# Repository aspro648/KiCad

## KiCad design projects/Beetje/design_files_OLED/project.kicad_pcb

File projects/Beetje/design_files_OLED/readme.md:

Beetje OLED

Project website: https://hackaday.io/project/160638-beetje-bloks

Based on SparkFun's [Micro OLED Breakout](https://www.sparkfun.com/products/13003)

Bill Of Materials
----------------

- 1 ea., Perfect Purple PCB from OSH Park, with not so perfect layout from [design_files](design_files/) folder.
- 1 ea., CrystalFonts display CFAL4864A, https://www.crystalfontz.com/product/cfal6448a066bw-64x48-small-graphic-oled
- 2 ea., R1, R2 RES 4K7 OHM 5% 0805, https://www.digikey.com/short/j2d0wd 
- 4 ea., R3 - R6 RES 10K OHM 5% 0805, 
- 1 ea., C1 CAP 1uF 0805, https://www.digikey.com/short/jwjfn1
- 2 ea., C2, C3 CAP CER 0.1UF 0805
- 1 ea., CONN FPC TOP 12POS 0.50MM R/A, TE 1-1734839-2, https://www.digikey.com/short/pzh9vc

Optional
----------------

- Headers

Revisions
------------------

License
----------------
[Attribution-ShareAlike 3.0 United States (CC BY-SA 3.0 US)](https://creativecommons.org/licenses/by-sa/3.0/us/)

You are free to:

- Share — copy and redistribute the material in any medium or format
- Adapt — remix, transform, and build upon the material

Under the following terms:

- Attribution — You must give appropriate credit, provide a link to the license, and indicate if changes were made. You may do so in any reasonable manner, but not in any way that suggests the licensor endorses you or your use.
- ShareAlike — If you remix, transform, or build upon the material, you must distribute your contributions under the same license as the original.

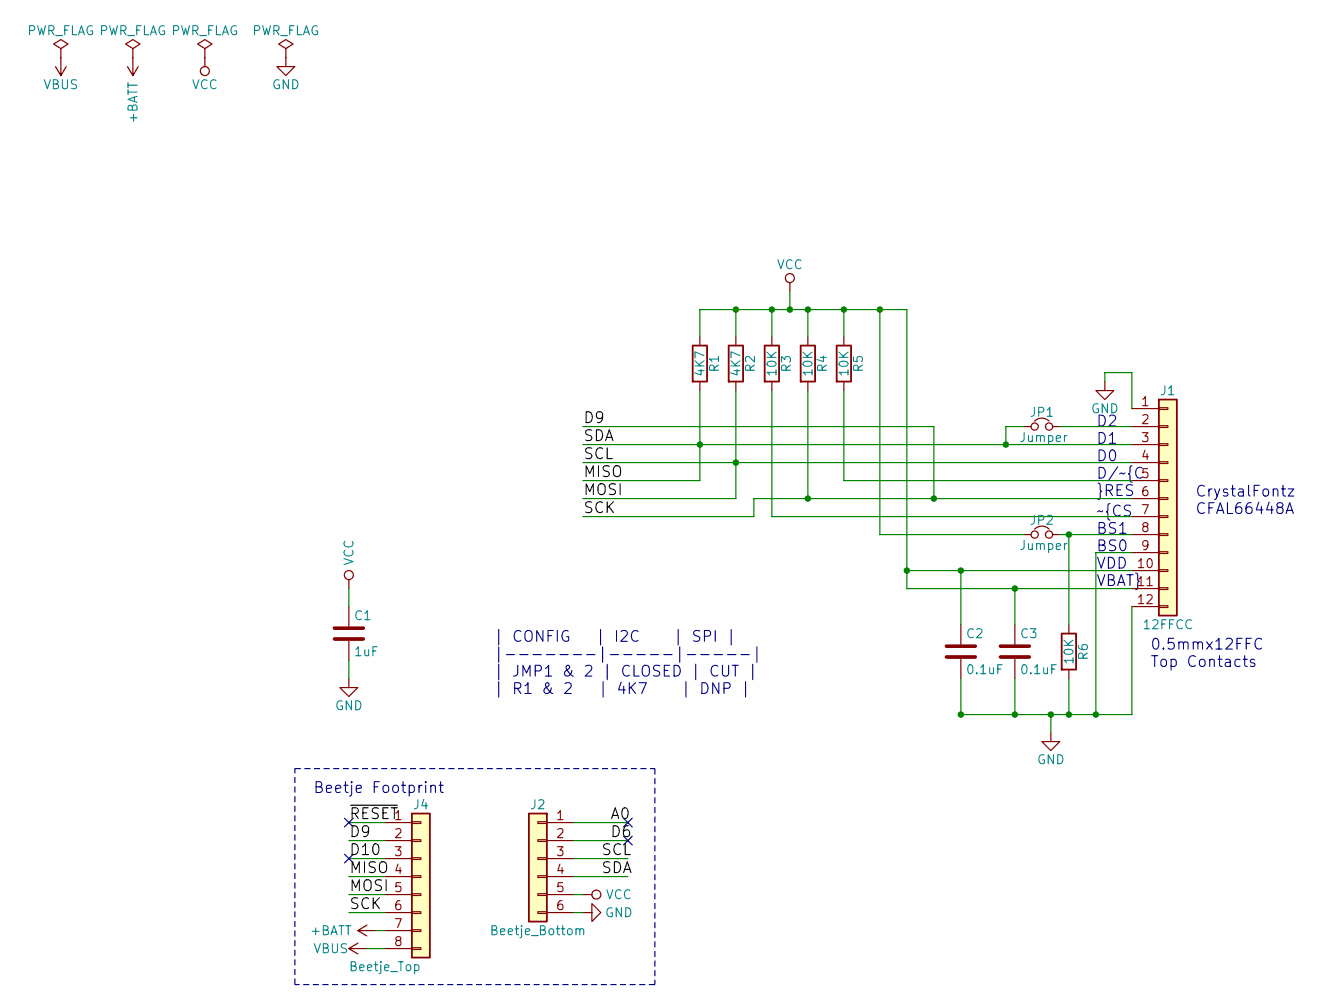
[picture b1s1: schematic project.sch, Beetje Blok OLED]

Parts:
C1: 1uF; C_0805_HandSoldering
C2, C3: 0.1uF; C_0805_HandSoldering
J1: 12FFCC; Hirose_FH12-11S-0.5SH_1x11-1MP_P0.50mm_Horizontal
J2: Beetje_Bottom
J4: Beetje_Top
JP1, JP2: Jumper
R1, R2: 4K7; R_0805_HandSoldering
R3, R4, R5, R6: 10K; R_0805_HandSoldering

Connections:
+BATT: J4.7
/A0: J2.1
/D6: J2.2
/D9: J1.6, J4.2, J4.6, R4.2
/D10: J4.3
/MISO: J1.3, J2.4, J4.4, JP1.1, R1.2
/MOSI: J1.4, J2.3, J4.5, R2.2
/~RESET: J4.1
GND: C1.2, C2.2, C3.2, J1.1, J1.9, J1.12, J2.6, R6.2
unnamed: J1.2, JP1.2
unnamed: J1.5, R5.2
unnamed: J1.7, R3.2
unnamed: J1.8, JP2.2, R6.1
VBUS: J4.8
VCC: C1.1, C2.1, C3.1, J1.10, J1.11, J2.5, JP2.1, R1.1, R2.1, R3.1, R4.1, R5.1

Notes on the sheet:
0.5mmx12FFC Top Contacts
D2 D1 D0 D/~C ~RES
~CS BS1 BS0 VDD VBAT
CrystalFontz CFAL66448A
| CONFIG | I2C | SPI | |-------|-----|-----| | JMP1 & 2 | CLOSED | CUT | | R1 & 2 | 4K7 | DNP |
Beetje Footprint

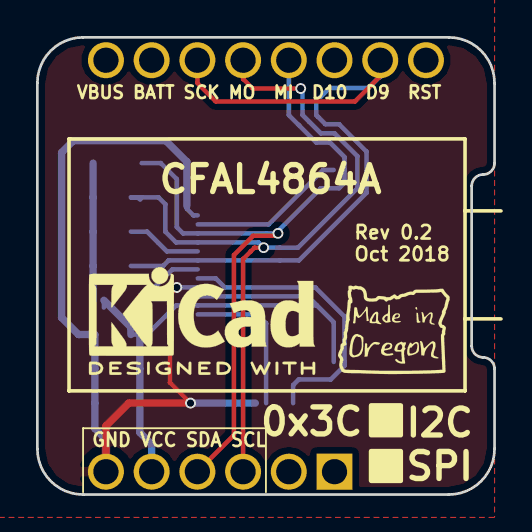
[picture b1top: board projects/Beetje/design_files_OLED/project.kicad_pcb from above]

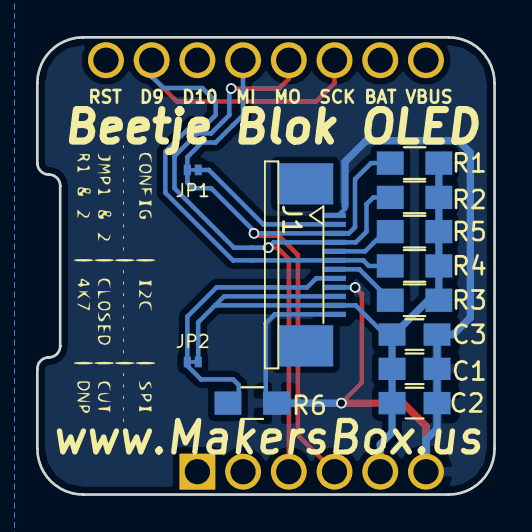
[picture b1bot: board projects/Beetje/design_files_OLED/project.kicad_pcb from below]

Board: 2 copper layers, 25.4 x 25.4 mm, 15 parts (13 on the bottom side), 9 nets.

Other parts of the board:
VAL: MadeInOregonRev25

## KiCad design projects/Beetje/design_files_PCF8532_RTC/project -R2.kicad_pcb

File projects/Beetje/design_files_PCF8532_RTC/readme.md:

Beetje RTC

Project website: https://hackaday.io/project/160638-beetje-bloks

Based on Adafruit's [PCF8523 Real Time Clock Assembled Breakout Board](https://www.adafruit.com/product/3295)

Bill Of Materials
----------------
  
- 1 ea., Perfect Purple PCB from OSH Park from [design_files](design_files/) folder.
- 1 ea., U1 IC RTC CLK/CALENDAR I2C 8-SOIC, NXP PCF8523T/1,118, https://www.digikey.com/short/j5n049
- 1 ea., Y1 CRYSTAL 32.7680KHZ 12.5PF 
	- 2-SMD, ECS ECS-.327-12.5-34B-TR, https://www.digikey.com/short/jfhppz
	- 4-SOJ, 5.50mm pitch ECS-.327-12.5-17X-TR https://www.digikey.com/short/zjc7d7
- 1 ea., R1 RES 1K OHM 5% 0805, https://www.digikey.com/short/j2d0wt
- 2 ea., R2-3 RES 4K7 OHM 5% 0805, https://www.digikey.com/short/j2d0wd 
- 1 ea., CAP CER 1UF 16V X7R 0805, https://www.digikey.com/short/z8dz2m
- 1 ea., C2 CAP 3.3uF 0805, https://www.digikey.com/short/jnw857
- 1 ea., BT1 CR1220 Holder, MPD BK-885-TR, https://www.digikey.com/short/jfhzc9
- 1 ea., 64-pin header(enough for 4.5 boards) Mill-max 311-43-164-41-001000, https://www.digikey.com/short/jnqdm2

Optional
----------------

- Headers

Revisions
------------------
0.2 2SMD CRYSTAL
0.3 Battery top.  Option of crystal.

License
----------------
[Attribution-ShareAlike 3.0 United States (CC BY-SA 3.0 US)](https://creativecommons.org/licenses/by-sa/3.0/us/)

You are free to:

- Share — copy and redistribute the material in any medium or format
- Adapt — remix, transform, and build upon the material

Under the following terms:

- Attribution — You must give appropriate credit, provide a link to the license, and indicate if changes were made. You may do so in any reasonable manner, but not in any way that suggests the licensor endorses you or your use.
- ShareAlike — If you remix, transform, or build upon the material, you must distribute your contributions under the same license as the original.

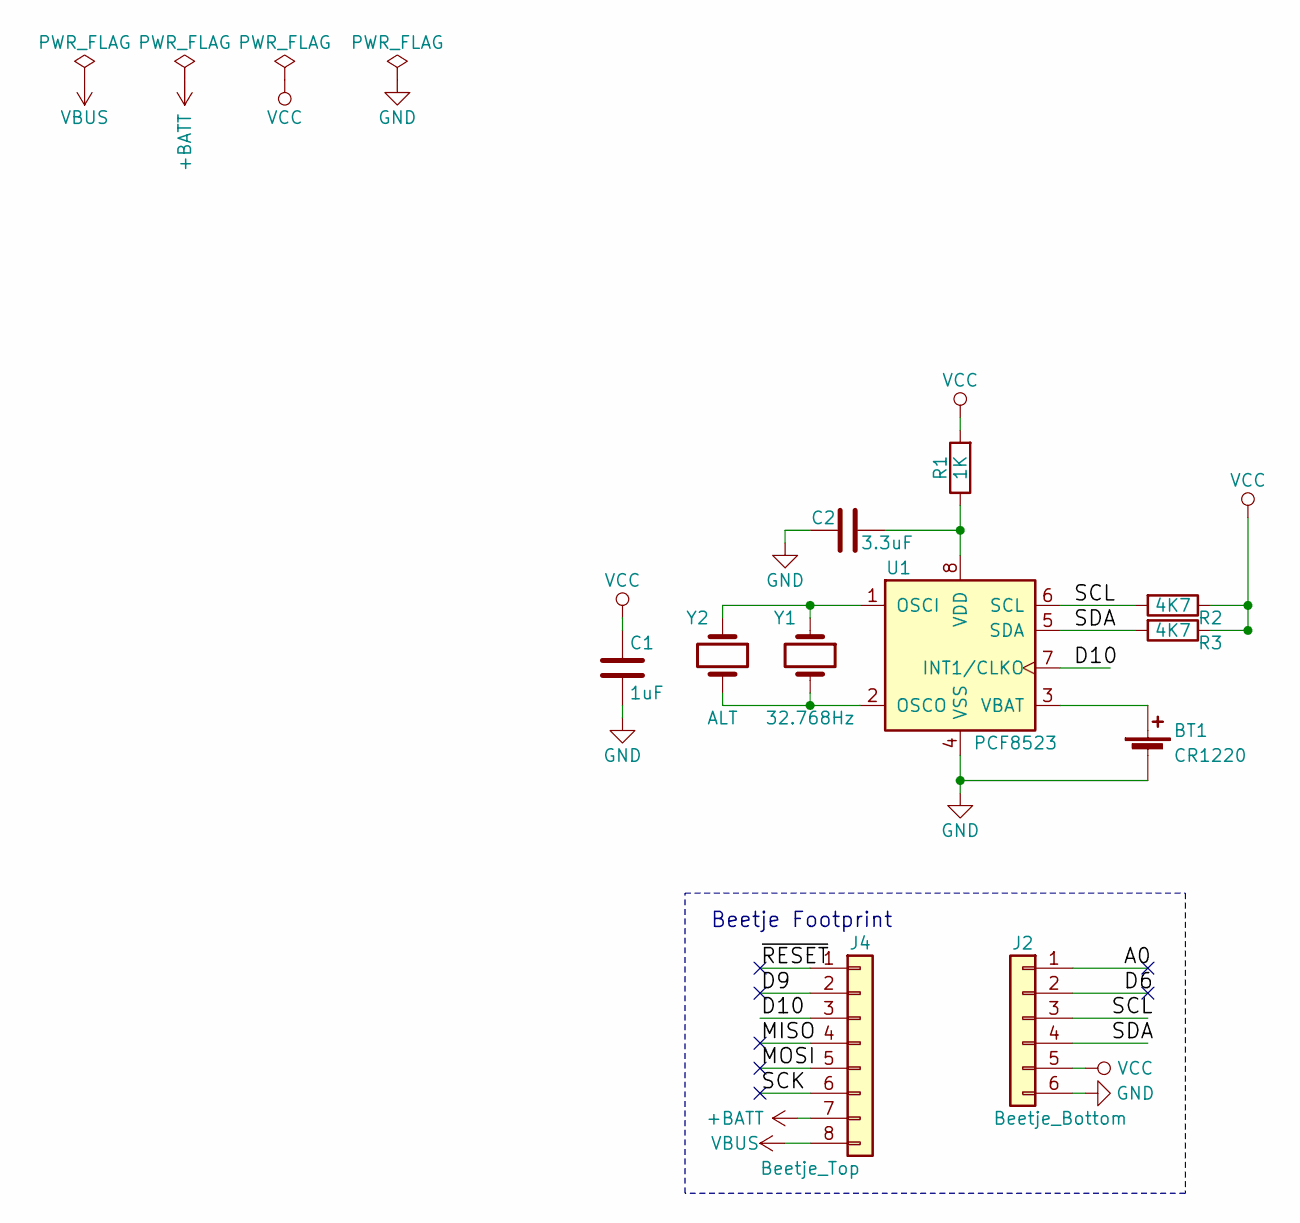
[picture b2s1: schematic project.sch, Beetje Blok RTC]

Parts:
BT1: CR1220; Keystone_3000_1x12mm-CoinCell
C1: 1uF; C_0805_HandSoldering
C2: 3.3uF; C_0805_HandSoldering
J2: Beetje_Bottom
J4: Beetje_Top
R1: 1K; R_0805_HandSoldering
R2, R3: 4K7; R_0805_HandSoldering
U1: PCF8523; SOIC-8_3.9x4.9mm_Pitch1.27mm
Y1: 32.768Hz; Crystal_SMD_G8-2pin_3.2x1.5mm_HandSoldering
Y2: ALT; Crystal_SMD_SeikoEpson_MC306-4pin_8.0x3.2mm

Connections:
+BATT: J4.7
/A0: J2.1
/D6: J2.2
/D9: J4.2
/D10: J4.3, U1.7 (INT1/CLKO)
/MISO: J4.4
/MOSI: J4.5
/SCK: J4.6
/SCL: J2.3, R2.2, U1.6 (SCL)
/SDA: J2.4, R3.2, U1.5 (SDA)
/~RESET: J4.1
GND: BT1.2 (-), C1.2, C2.2, J2.6, U1.4 (VSS)
unnamed: BT1.1 (+), U1.3 (VBAT)
unnamed: C2.1, R1.1, U1.8 (VDD)
unnamed: U1.1 (OSCI), Y1.1, Y2.1
unnamed: U1.2 (OSCO), Y1.2, Y2.2
VBUS: J4.8
VCC: C1.1, J2.5, R1.2, R2.1, R3.1

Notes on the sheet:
Beetje Footprint

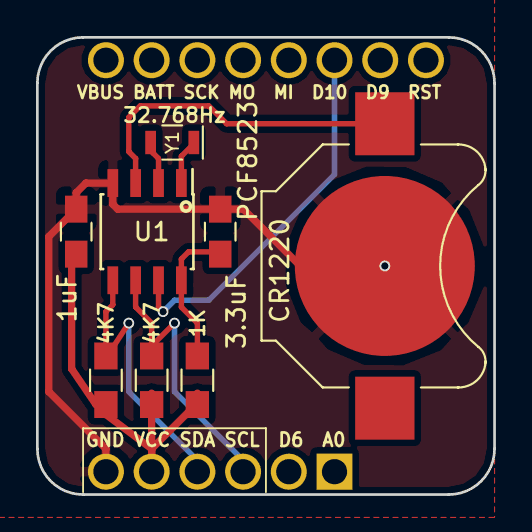
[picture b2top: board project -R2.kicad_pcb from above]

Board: 2 copper layers, 25.4 x 25.4 mm, 11 parts (0 on the bottom side), 9 nets.

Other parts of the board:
VAL: MadeInOregonRev25

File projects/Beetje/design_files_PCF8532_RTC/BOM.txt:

Beetje Blok PCF8523T RTC Rev 0.0

Bill Of Materials
----------------
  
- 1 ea., Perfect Purple PCB from OSH Park from [design_files](design_files/) folder.
- 1 ea., U1 IC RTC CLK/CALENDAR I2C 8-SOIC, NXP PCF8523T/1,118, https://www.digikey.com/short/j5n049
- 1 ea., Y1 CRYSTAL 32.7680KHZ 12.5PF 4-SMD, ECS ECS-.327-12.5-17X-TR, https://www.digikey.com/short/j5n0pn
or?
- 1 ea., Y2 CRYSTAL 32.7680KHZ 12.5PF 2-SMD, ECS ECS-.327-12.5-34B-TR, https://www.digikey.com/short/jfhppz
- 1 ea., R1 RES 1K OHM 5% 0603, https://www.digikey.com/short/jfhzq7
- 2 ea., R2-3 RES 4K7 OHM 5% 0603, https://www.digikey.com/short/jfhzqr 
- 1 ea., C1 CAP 1uF 0603, https://www.digikey.com/short/jfhzjq
- 1 ea., C2 CAP 3.3uF 0603, https://www.digikey.com/short/jfhz8r
- 1 ea., CONN HEADER .100" SNGL STR 40POS, https://www.digikey.com/short/jfcn42
- 1 ea., BT1 CR1220 Holder, MPD BK-885-TR, https://www.digikey.com/short/jfhzc9

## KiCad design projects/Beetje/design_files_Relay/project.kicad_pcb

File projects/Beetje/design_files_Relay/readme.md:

Beetje Relay

Project website: https://hackaday.io/project/160638-beetje-bloks

Bill Of Materials
----------------
  
- 1 ea., Perfect Purple PCB from OSH Park, with not so perfect layout from [project.kicad_pcb](project.kicad_pcb) file.
- 1 ea., RLY1 RELAY GEN PURPOSE DPDT 2A 250V, https://www.digikey.com/short/jwfmr5
- 1 ea., Q1 TRANS NPN 40V 0.2A SOT23, MMBT3904-TP, https://www.digikey.com/short/jbpvh0
- 1 ea., D2 LED SMD 0805, https://www.digikey.com/short/jwf4nw
- 1 ea., R2 1K SMD 0805, https://www.digikey.com/short/j2d0wt
- 2 ea., J1, J3 TERM BLOCK PCB 2POS 5.0MM GREEN, Phoenix 1935161 https://www.digikey.com/short/jnrmvw
- 1 ea., 64-pin header(enough for 4.5 boards) Mill-max 311-43-164-41-001000, https://www.digikey.com/short/jnqdm2

Revisions
------------------
0.1 Moved relay to avoid short on USB. Removed full fills to avoid shorts if using AC in relay. 
    Added messages about possible HV or AC on relay pins.
	Changed to 3.5mm terminal for 12 AWG wire.

License
----------------
[Attribution-ShareAlike 3.0 United States (CC BY-SA 3.0 US)](https://creativecommons.org/licenses/by-sa/3.0/us/)

You are free to:

- Share — copy and redistribute the material in any medium or format
- Adapt — remix, transform, and build upon the material

Under the following terms:

- Attribution — You must give appropriate credit, provide a link to the license, and indicate if changes were made. You may do so in any reasonable manner, but not in any way that suggests the licensor endorses you or your use.
- ShareAlike — If you remix, transform, or build upon the material, you must distribute your contributions under the same license as the original.

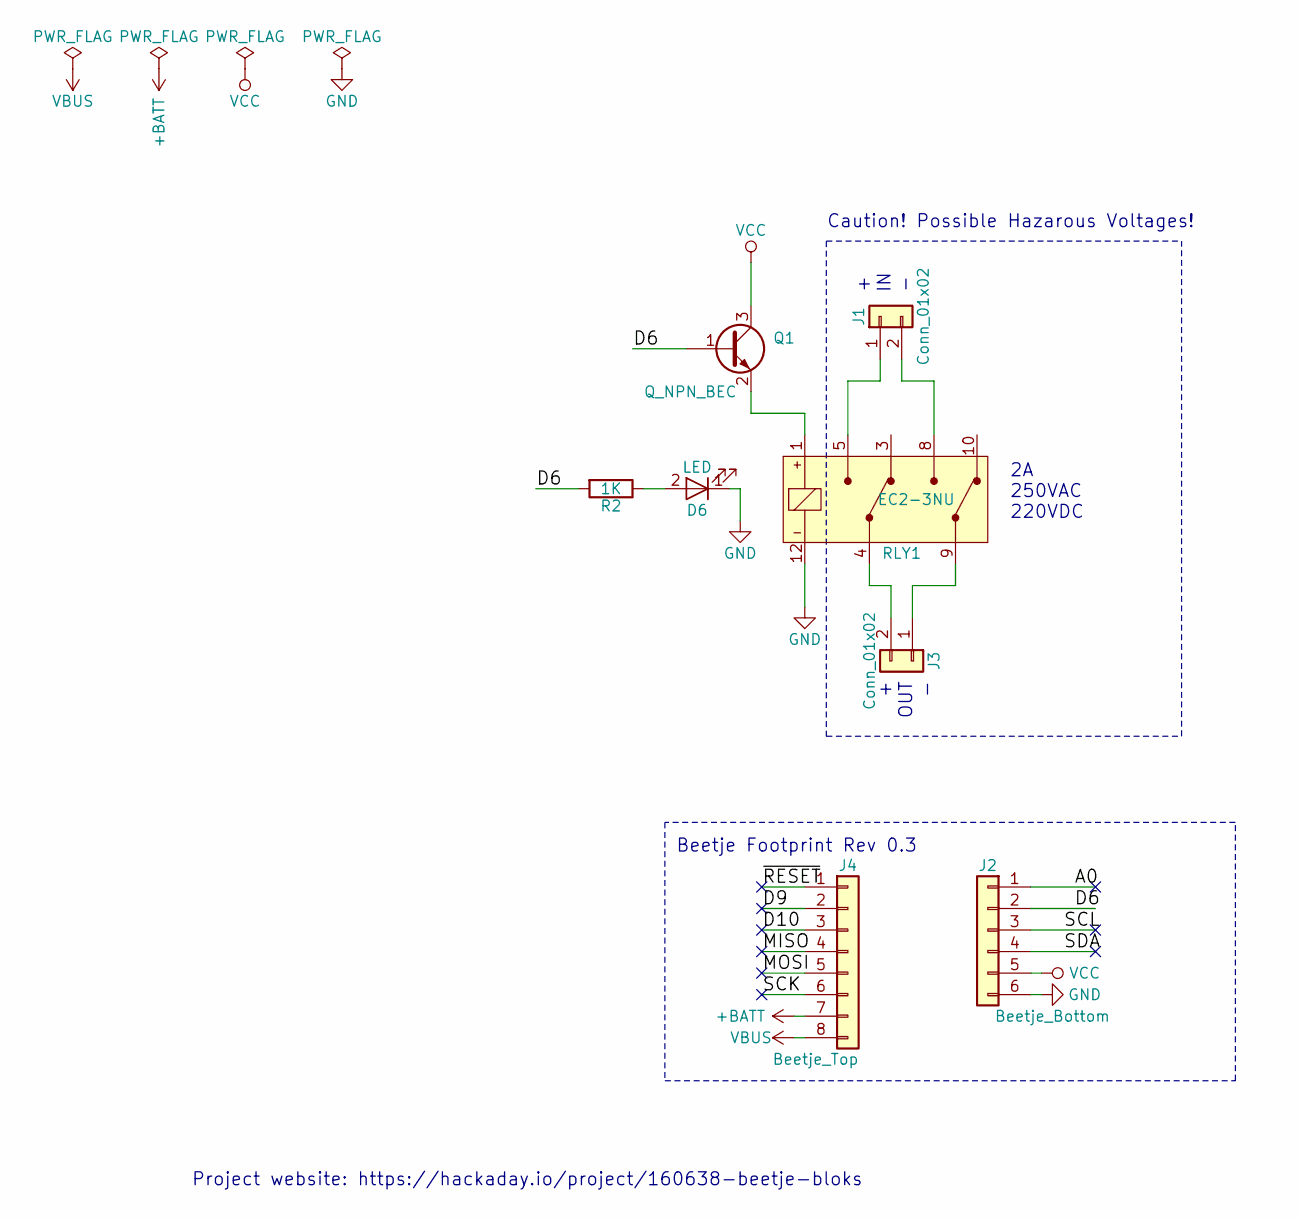
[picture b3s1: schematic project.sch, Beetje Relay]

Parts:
D6: LED; LED_0805_HandSoldering
J1, J3: Conn_01x02; TerminalBlock_bornier-2_P5.08mm
J2: Beetje_Bottom
J4: Beetje_Top
Q1: Q_NPN_BEC; SOT-23
R2: 1K; R_0805_HandSoldering
RLY1: EC2-3NU; Relay_THT_EC2; MPN EC2-5NU; Digi-Key_PN 399-11052-5-ND

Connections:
+BATT: J4.7
/A0: J2.1
/D6: J2.2, Q1.1 (B), R2.2
/D9: J4.2
/D10: J4.3
/MISO: J4.4
/MOSI: J4.5
/SCK: J4.6
/SCL: J2.3
/SDA: J2.4
/~RESET: J4.1
GND: D6.1 (K), J2.6, RLY1.12 (COIL)
unnamed: D6.2 (A), R2.1
unnamed: J1.1, RLY1.5 (NO1)
unnamed: J1.2, RLY1.8 (NO2)
unnamed: J3.1, RLY1.9 (COM2)
unnamed: J3.2, RLY1.4 (COM1)
unnamed: Q1.2 (E), RLY1.1 (COIL)
VBUS: J4.8
VCC: J2.5, Q1.3 (C)

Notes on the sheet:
Beetje Footprint Rev 0.3
Project website: https://hackaday.io/project/160638-beetje-bloks
+ IN -
+ OUT -
2A 250VAC 220VDC
Caution! Possible Hazarous Voltages!

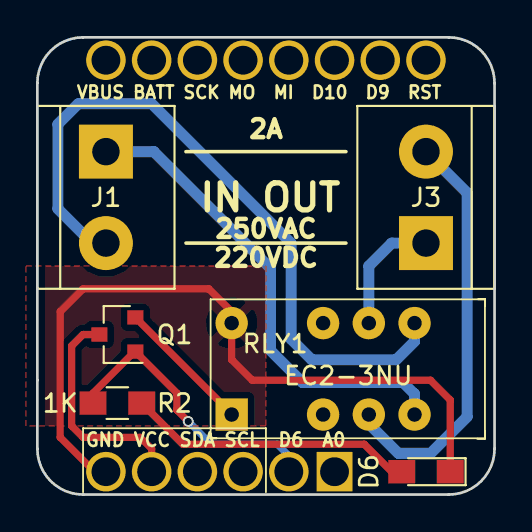
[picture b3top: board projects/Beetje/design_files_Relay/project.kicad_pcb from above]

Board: 2 copper layers, 25.4 x 25.4 mm, 9 parts (0 on the bottom side), 9 nets.

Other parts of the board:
VAL: MadeInOregonRev25

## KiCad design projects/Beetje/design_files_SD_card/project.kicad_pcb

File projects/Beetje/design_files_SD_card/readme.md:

Beetje Blok SD Card Rev 0.0

Project website: https://hackaday.io/project/160638-beetje-bloks

Project website: https://hackaday.io/project/160638-beetje-bloks

https://learn.adafruit.com/adafruit-micro-sd-breakout-board-card-tutorial?view=all

Bill Of Materials
----------------
  
- 1 ea., Perfect Purple PCB from OSH Park, with not so perfect layout from [design_files](design_files/) folder.
- 1 ea., J1 CONN MICRO SD CARD PUSH-PULL, Hirose DM3D-SF, https://www.digikey.com/short/jfh304
- 1 ea., C1 CAP CER 0.1UF 50V X7R 0805, https://www.digikey.com/short/j58qjp
- 1 ea., D1 LED 0805 SMD
- 1 ea., R1 RES 1K OHM 5% 0805, https://www.digikey.com/short/j2d0wt
- 1 ea., R2 10K SMD 0805, https://www.digikey.com/short/j2d0w4 
- 1 ea., CONN HEADER .100" SNGL STR 40POS, https://www.digikey.com/short/jfcn42
- 1 ea., 64-pin header(enough for 4.5 boards) Mill-max 311-43-164-41-001000, https://www.digikey.com/short/jnqdm2

License
----------------
[Attribution-ShareAlike 3.0 United States (CC BY-SA 3.0 US)](https://creativecommons.org/licenses/by-sa/3.0/us/)

You are free to:

- Share — copy and redistribute the material in any medium or format
- Adapt — remix, transform, and build upon the material

Under the following terms:

- Attribution — You must give appropriate credit, provide a link to the license, and indicate if changes were made. You may do so in any reasonable manner, but not in any way that suggests the licensor endorses you or your use.
- ShareAlike — If you remix, transform, or build upon the material, you must distribute your contributions under the same license as the original.

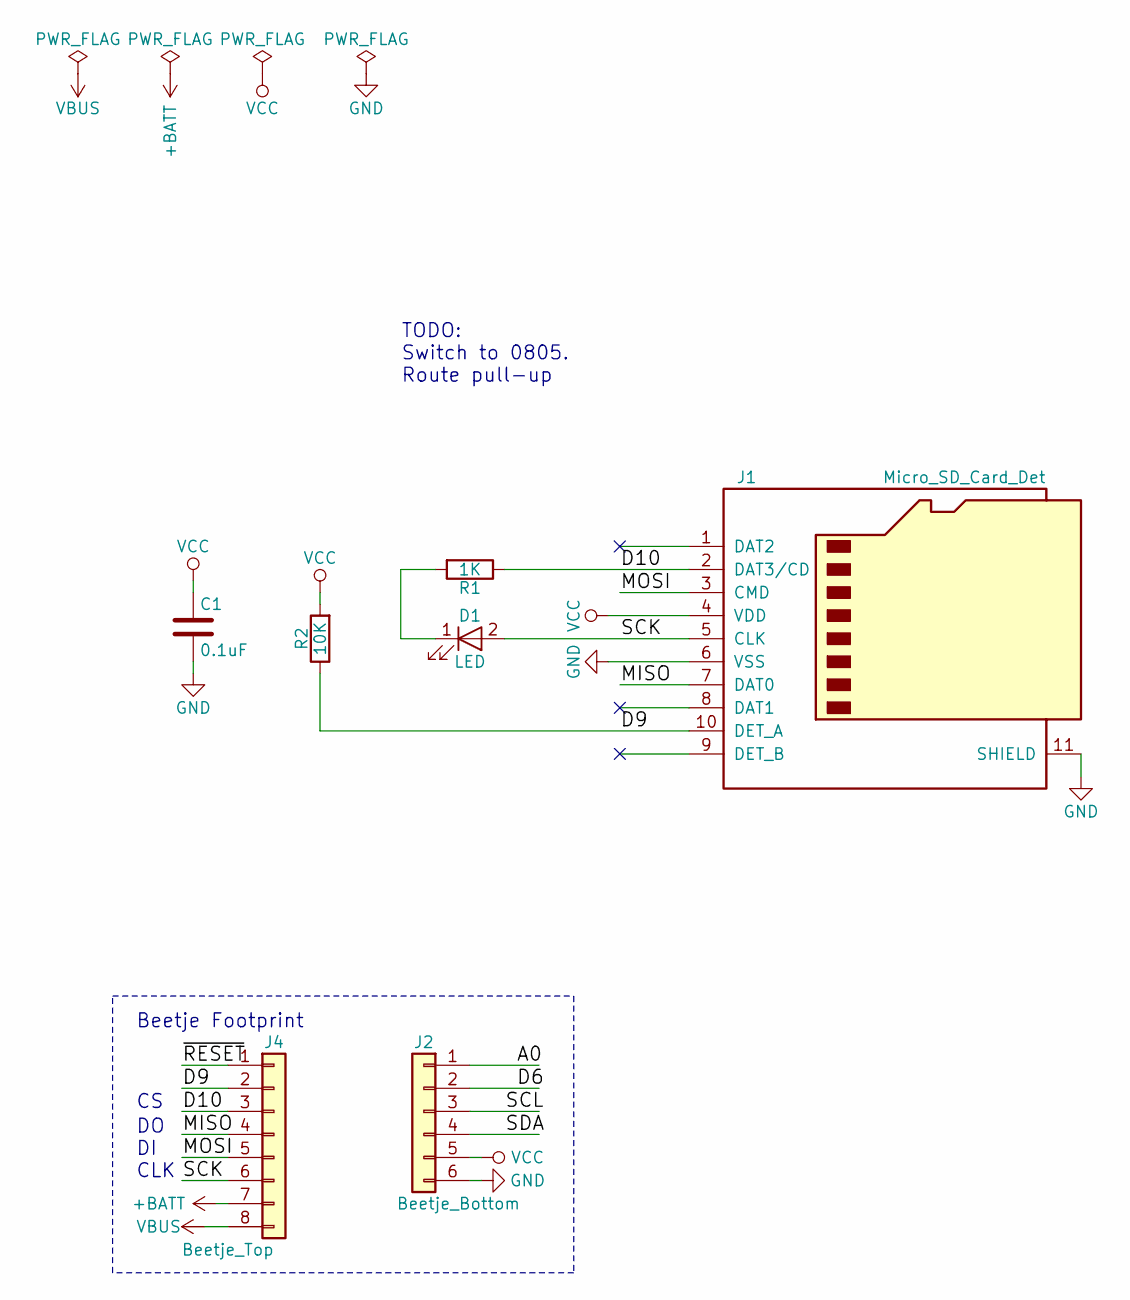
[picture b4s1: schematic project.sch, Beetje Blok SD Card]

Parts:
C1: 0.1uF; C_0805_HandSoldering
D1: LED; LED_0603
J1: Micro_SD_Card_Det; Hirose_DM3D-SF
J2: Beetje_Bottom
J4: Beetje_Top
R1: 1K; R_0805_HandSoldering
R2: 10K; R_0805_HandSoldering

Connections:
+BATT: J4.7
/A0: J2.1
/D6: J2.2
/D9: J1.10 (DET_A), J4.2, R2.1
/D10: J1.2 (DAT3/CD), J4.3, R1.1
/MISO: J1.7 (DAT0), J4.4
/MOSI: J1.3 (CMD), J4.5
/SCK: D1.2 (A), J1.5 (CLK), J4.6
/SCL: J2.3
/SDA: J2.4
/~RESET: J4.1
GND: C1.2, J1.6 (VSS), J1.11 (SHIELD), J2.6
unnamed: D1.1 (K), R1.2
VBUS: J4.8
VCC: C1.1, J1.4 (VDD), J2.5, R2.2

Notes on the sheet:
DO DI CLK
TODO: Switch to 0805. Route pull-up
Beetje Footprint

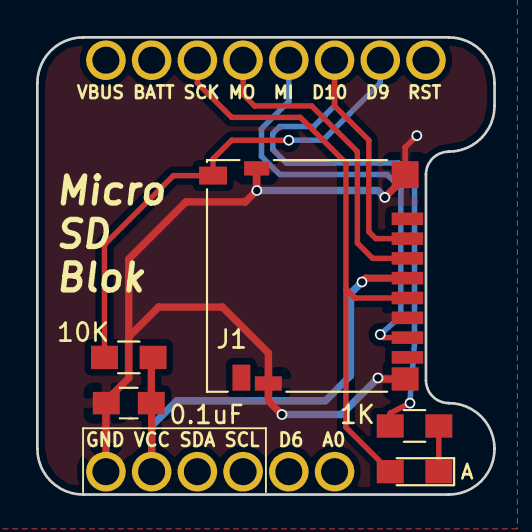
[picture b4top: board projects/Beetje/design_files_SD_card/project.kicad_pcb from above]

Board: 2 copper layers, 25.4 x 25.4 mm, 8 parts (0 on the bottom side), 8 nets.

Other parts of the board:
VAL: MadeInOregonRev25

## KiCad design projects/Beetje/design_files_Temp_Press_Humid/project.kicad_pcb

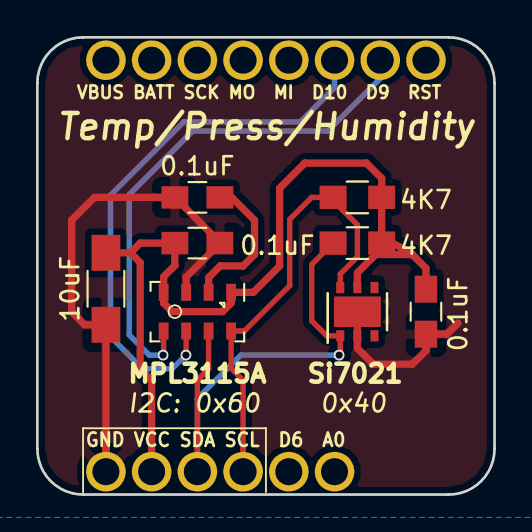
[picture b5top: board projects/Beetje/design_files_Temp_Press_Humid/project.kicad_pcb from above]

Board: 2 copper layers, 25.4 x 25.4 mm, 11 parts (0 on the bottom side), 7 nets.

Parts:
C1, C3, C4: 0.1uF; C_0805_HandSoldering
C2: 10uF; C_1206_HandSoldering
J2: Beetje_Bottom
J4: Beetje_Top
R1, R2: 4K7; R_0805_HandSoldering
U1: Si7021; DFN-6-1EP_3x3mm_Pitch0.95mm
U2: MPL3115A
VAL: MadeInOregonRev25

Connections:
/D9: J4.2, U2.5
/D10: J4.3, U2.6
/SCL: J2.3, R1.2, U1.6, U2.8
/SDA: J2.4, R2.2, U1.1, U2.7
GND: C1.2, C2.2, C3.2, C4.2, J2.6, U1.2, U1.7, U2.3
unnamed: C4.1, U2.2
VCC: C1.1, C2.1, C3.1, J2.5, R1.1, R2.1, U1.5, U2.1, U2.4

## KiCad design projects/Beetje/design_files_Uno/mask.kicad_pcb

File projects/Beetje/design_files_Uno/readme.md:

Leo, the Arduino Leonardo clone

https://rheingoldheavy.com/arduino-from-scratch-part-5-selecting-comparator-parts/

Bill Of Materials
----------------
  
- 1 ea., Perfect Purple PCB from OSH Park, with not so perfect kicad.pcb file.
- 1 ea., U1 IC REG LINEAR 3.3V 150MA SOT23-5, LP2985-33DBVRG4, https://www.digikey.com/short/j29pqr
- 1 ea., U2 IC OPAMP GP 1MHZ RRO 8VSSOP, LMV358IDGKR, https://www.digikey.com/short/j29pj7
- 1 ea., U4 ATMEGA32U4-AU, IC MCU 8BIT 32KB FLASH 44TQFP, https://www.digikey.com/short/jb25pc
- 1 ea., U3 IC REG LINEAR 5V 1A SOT223 NCP1117ST50T3G, https://www.digikey.com/short/j29pqc
- 1 ea., Q1 MOSFET P-CH 20V 2A SSOT3, FDN340P, https://www.digikey.com/short/j29ppj

- 1 ea., Y1 CER RES 16.0000MHZ 15PF SMD, CSTCE16M0V53-R0, https://www.digikey.com/short/j2b9cm
- 2 ea., C3, C6, C7 CAP CER 10UF 25V 1206, https://www.digikey.com/short/j29pwm
- 2 ea., C1, C5 CAP CER 1UF SMD 0805
- 1 ea., C4 CAP CER 0.1UF SMD 0805
- 1 ea., C2 CAP CER 22pF SMD 0805

- 1 ea., F1 PTC 1206, Bel 0ZCJ0025AF2E, https://www.digikey.com/short/jfcbc8
- 2 ea., RV1, RV2 VARISTOR 	VARISTOR 10.8V 40A 0805, https://www.digikey.com/short/jwj45d
- 4 ea., R1-R4 Resistor 1K OHM SMD 0805, https://www.digikey.com/short/j2d0wt
- 2 ea., R5, R8 Resistor 10K OHM SMD 0805, https://www.digikey.com/short/j2d0w4
- 2 ea., R6, R7 Resistor 22 OHM SMD 0805, https://www.digikey.com/short/jwj45j
- 1 ea., R9 Resistor 1M OHM SMD 0603, 
- 4 ea., D1-D4 SMD LED 0805, https://www.digikey.com/short/jwj4rb

- 1 ea., SW1 SWITCH TACTILE SPST-NO 0.05A 12V, SW416-ND, https://www.digikey.com/short/jwj4m9
- 1 ea., X3, CONN RCPT MICRO USB R/A SMD, Molex 1050170001, https://www.digikey.com/short/jb2205
- 1 ea., J1 Barrel Jack, https://www.digikey.com/short/j2fz43
- 1 ea., 6-Pin header, https://www.digikey.com/short/jwj4w4
- 2 ea., 8-Pin header, https://www.digikey.com/short/jwj4dp
- 1 ea., 10-Pin header, https://www.digikey.com/short/jwj4n7

License
----------------
[Attribution-ShareAlike 3.0 United States (CC BY-SA 3.0 US)](https://creativecommons.org/licenses/by-sa/3.0/us/)

You are free to:

- Share — copy and redistribute the material in any medium or format
- Adapt — remix, transform, and build upon the material

Under the following terms:

- Attribution — You must give appropriate credit, provide a link to the license, and indicate if changes were made. You may do so in any reasonable manner, but not in any way that suggests the licensor endorses you or your use.
- ShareAlike — If you remix, transform, or build upon the material, you must distribute your contributions under the same license as the original.

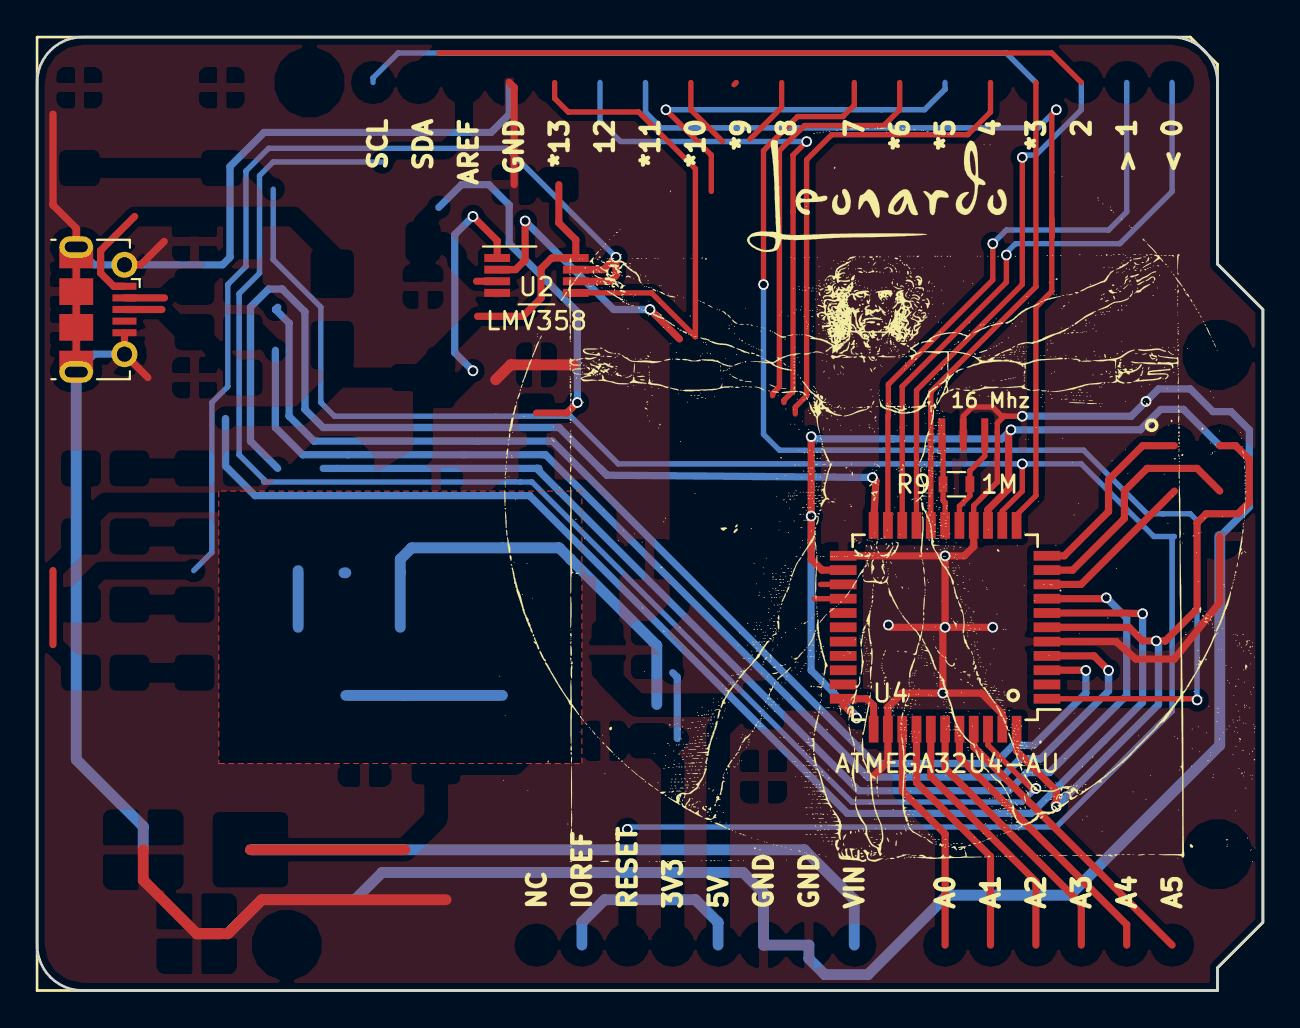
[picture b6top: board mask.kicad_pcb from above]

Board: 2 copper layers, 68.6 x 53.3 mm, 6 parts (0 on the bottom side), 6 nets.

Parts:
R9: 1M; R_0603
U2: LMV358; VSSOP-8_3.0x3.0mm_Pitch0.65mm
U4: ATMEGA32U4-AU; TQFP-44_10x10mm_Pitch0.8mm
X1: USB_OTG; USB_Micro-B_Molex-105017-0001
XA1: Arduino_Leonardo_Shield
Y1: 16 Mhz; Resonator_SMD_CTSC_1.3mmx3.2mm

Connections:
+5V: U2.8, U4.6, U4.14, U4.24, U4.33, U4.34, U4.44
/D13: U2.5, U4.32
GND: U2.4, U4.5, U4.15, U4.23, U4.35, U4.43, X1.5, X1.6, Y1.2
unnamed: U2.6, U2.7
unnamed: R9.1, U4.16, Y1.3
unnamed: R9.2, U4.17, Y1.1

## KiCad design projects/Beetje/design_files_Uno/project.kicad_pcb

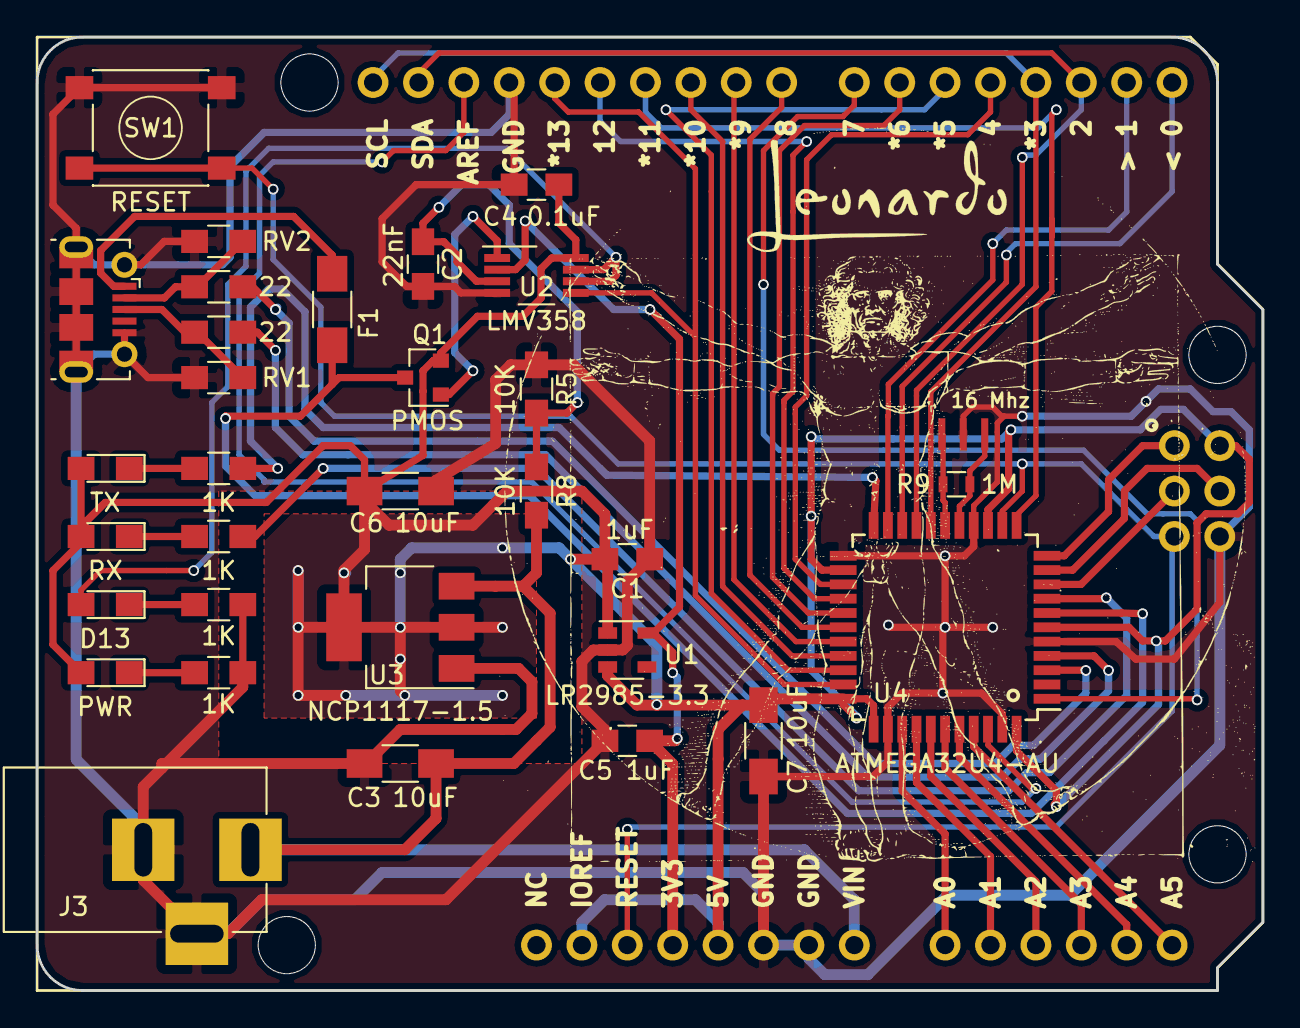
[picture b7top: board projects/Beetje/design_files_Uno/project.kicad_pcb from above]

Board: 2 copper layers, 68.6 x 53.3 mm, 34 parts (0 on the bottom side), 46 nets.

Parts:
C1, C5: 1uF; C_0805_HandSoldering
C2: 22nF; C_0805_HandSoldering
C3, C6, C7: 10uF; C_1206_HandSoldering
C4: 0.1uF; C_0805_HandSoldering
D1: PWR; LED_0805_HandSoldering
D2: TX; LED_0805_HandSoldering
D3: RX; LED_0805_HandSoldering
D4: D13; LED_0805_HandSoldering
F1: Polyfuse; R_1206_HandSoldering
J3: Barrel_Jack; BARREL_JACK
Q1: PMOS; SOT-23
R1, R2, R3, R4: 1K; R_0805_HandSoldering
R5, R8: 10K; R_0805_HandSoldering
R6, R7: 22; R_0805_HandSoldering
R9: 1M; R_0603
RV1, RV2: Varistor; R_0805_HandSoldering
SW1: RESET; SW_SPST_PTS645
U1: LP2985-3.3; SOT-23-5
U2: LMV358; VSSOP-8_3.0x3.0mm_Pitch0.65mm
U3: NCP1117-1.5; SOT-223-3_TabPin2
U4: ATMEGA32U4-AU; TQFP-44_10x10mm_Pitch0.8mm
VAL: MadeInOregonRev25
X1: USB_OTG; USB_Micro-B_Molex-105017-0001
XA1: Arduino_Leonardo_Shield
Y1: 16 Mhz; Resonator_SMD_CTSC_1.3mmx3.2mm

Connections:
+3V3: C5.1, U1.5, U2.2, XA1.3V3
+5V: C1.1, C4.1, C6.1, C7.1, D1.2, D2.2, D3.2, Q1.2, U1.1, U1.3, U2.8, U3.2, U4.6, U4.14, U4.24, U4.33, U4.34, U4.44, XA1.5V1, XA1.5V2, XA1.IORF
/A0: U4.36, XA1.A0
/A1: U4.37, XA1.A1
/A2: U4.38, XA1.A2
/A3: U4.39, XA1.A3
/A4: U4.40, XA1.A4
/A5: U4.41, XA1.A5
/AREF: U4.42, XA1.AREF
/D0: U4.20, XA1.D0
/D1: U4.21, XA1.D1
/D4: U4.25, XA1.D4
/D5: U4.31, XA1.D5
/D6: U4.27, XA1.D6
/D7: U4.1, XA1.D7
/D8: U4.28, XA1.D8
/D9: U4.29, XA1.D9
/D10: U4.30, XA1.D10
/D11: U4.12, XA1.D11
/D12: U4.26, XA1.D12
/D13: U2.5, U4.32, XA1.D13
/D+: R6.1, U4.4
/D-: R7.1, U4.3
/MISO: U4.11, XA1.MISO
/MOSI: U4.10, XA1.MOSI
/RXLED: R3.1, U4.8
/SCK: U4.9, XA1.SCK
/SCL: U4.18, XA1.D3, XA1.SCL
/SDA: U4.19, XA1.D2, XA1.SDA
/TXLED: R2.1, U4.22
/VIN: C3.1, J3.1, R8.2, U3.3, XA1.VIN
/~RESET: SW1.2, U4.13, XA1.RST1, XA1.RST2
GND: C1.2, C2.2, C3.2, C4.2, C5.2, C6.2, C7.2, J3.2, J3.3, R1.2, R4.2, R5.1, RV1.2, RV2.2, SW1.1, U1.2, U2.4, U3.1, U4.5, U4.15, U4.23, U4.35, U4.43, X1.5, X1.6, XA1.GND1, XA1.GND2, XA1.GND3, XA1.GND4, Y1.2
unnamed: C2.1, R5.2, R8.1, U2.3
unnamed: D1.1, R1.1
unnamed: D2.1, R2.2
unnamed: D3.1, R3.2
unnamed: D4.1, R4.1
unnamed: D4.2, U2.6, U2.7
unnamed: F1.2, X1.1
unnamed: Q1.1, U2.1
unnamed: R6.2, RV1.1, X1.3
unnamed: R7.2, RV2.1, X1.2
unnamed: R9.1, U4.16, Y1.3
unnamed: R9.2, U4.17, Y1.1
VBUS: F1.1, Q1.3, U4.7
